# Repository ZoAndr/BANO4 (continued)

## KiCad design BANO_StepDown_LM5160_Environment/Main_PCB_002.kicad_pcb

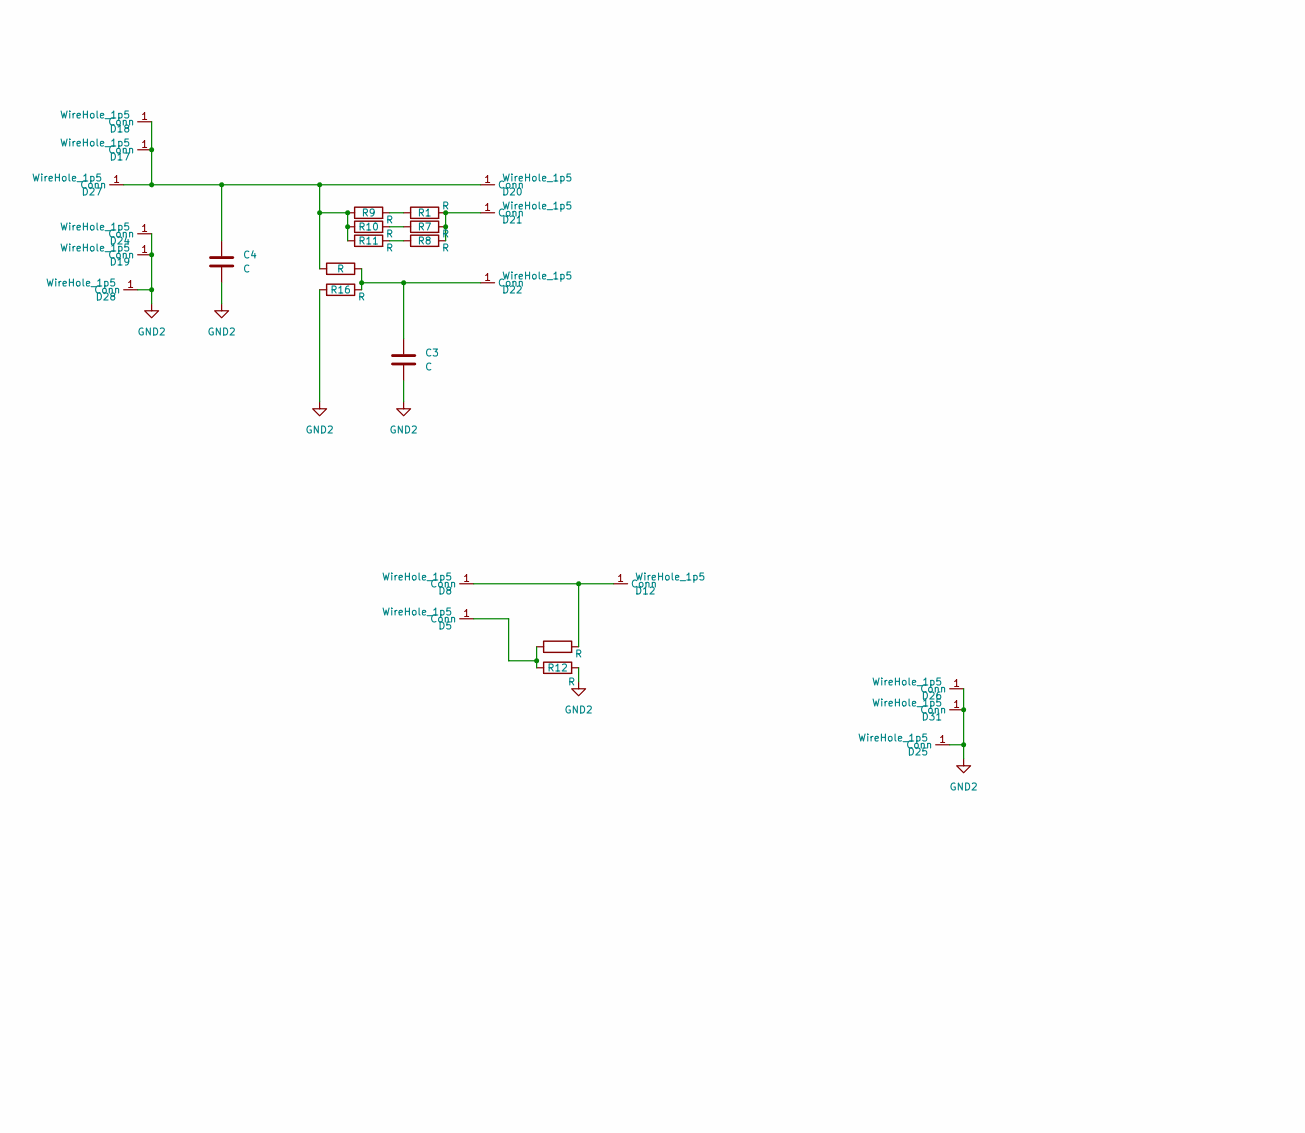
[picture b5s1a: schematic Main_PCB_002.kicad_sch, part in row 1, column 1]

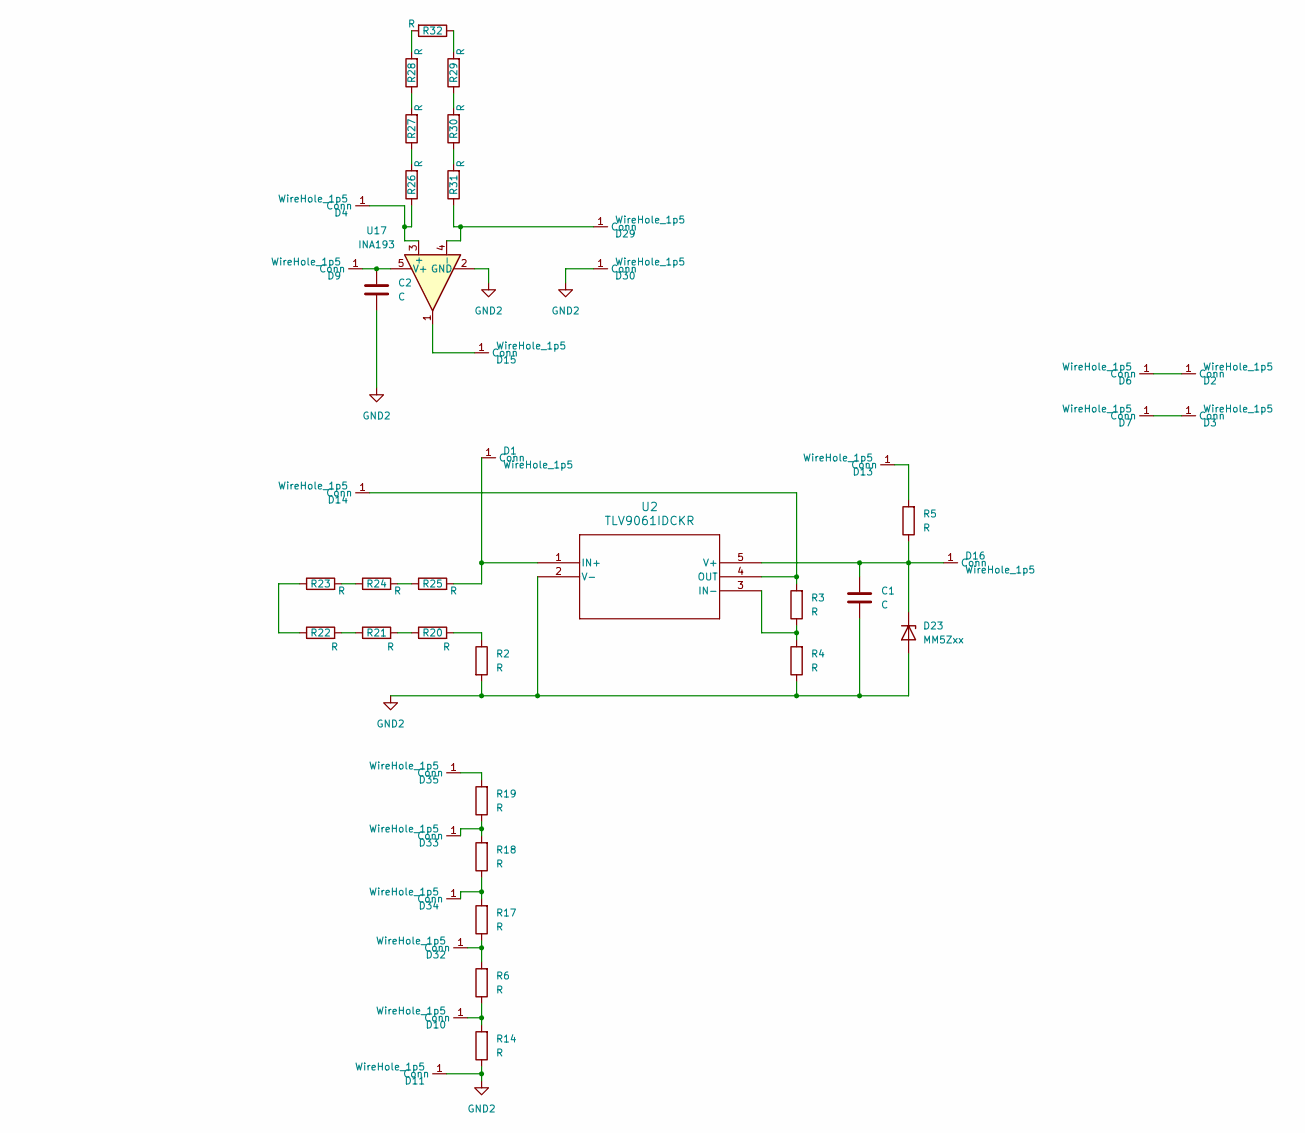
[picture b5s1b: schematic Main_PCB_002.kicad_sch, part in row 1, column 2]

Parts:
C1, C2, C3, C4: C; C_0603_1608Metric_Pad1.08x0.95mm_HandSolder
D1, D2, D3, D4, D5, D6, D7, D8, D9, D10, D11, D12, D13, D14, D15, D16, D17, D18, D19, D20, D21, D22, D24, D25, D26, D27, D28, D29, D30, D31, D32, D33, D34, D35: WireHole_1p5; WireHole_1p2
D23: MM5Zxx; D_SOD-523
R1, R2, R3, R4, R5, R7, R8, R9, R10, R11, R12, R13, R15, R16, R20, R21, R22, R23, R24, R25, R26, R27, R28, R29, R30, R31, R32: R; R_0603_1608Metric_Pad0.98x0.95mm_HandSolder
R6, R14, R17, R18, R19: R; R_2512_6332Metric_Pad1.40x3.35mm_HandSolder
U2: TLV9061IDCKR; DCK5_TEX
U17: INA193; SOT-23-5

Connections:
GND2: C1.2, C2.2, C3.2, C4.2, D11.1 (Conn), D19.1 (Conn), D23.2 (A), D24.1 (Conn), D25.1 (Conn), D26.1 (Conn), D28.1 (Conn), D30.1 (Conn), D31.1 (Conn), R2.2, R4.1, R12.2, R14.1, R16.2, U2.2 (V-), U17.2 (GND)
unnamed: D1.1 (Conn), R25.2, U2.1 (IN+)
unnamed: D2.1 (Conn), D6.1 (Conn)
unnamed: D3.1 (Conn), D7.1 (Conn)
unnamed: D4.1 (Conn), R26.1, U17.3 (+)
unnamed: D5.1 (Conn), R12.1, R13.1
unnamed: C2.1, D9.1 (Conn), U17.5 (V+)
unnamed: D10.1 (Conn), R6.1, R14.2
unnamed: D8.1 (Conn), D12.1 (Conn), R13.2
unnamed: D13.1 (Conn), R5.2
unnamed: D14.1 (Conn), R3.2, U2.4 (OUT)
unnamed: D15.1 (Conn), U17.1
unnamed: C1.1, D16.1 (Conn), D23.1 (K), R5.1, U2.5 (V+)
unnamed: C4.1, D17.1 (Conn), D18.1 (Conn), D20.1 (Conn), D27.1 (Conn), R9.1, R10.1, R11.1, R15.2
unnamed: D21.1 (Conn), R1.2, R7.2, R8.2
unnamed: C3.1, D22.1 (Conn), R15.1, R16.1
unnamed: D29.1 (Conn), R31.1, U17.4 (-)
unnamed: D32.1 (Conn), R6.2, R17.1
unnamed: D33.1 (Conn), R18.2, R19.1
unnamed: D34.1 (Conn), R17.2, R18.1
unnamed: D35.1 (Conn), R19.2
unnamed: R1.1, R9.2
unnamed: R2.1, R20.2
unnamed: R7.1, R10.2
unnamed: R8.1, R11.2
unnamed: R20.1, R21.2
unnamed: R21.1, R22.2
unnamed: R22.1, R23.1
unnamed: R23.2, R24.1
unnamed: R24.2, R25.1
unnamed: R26.2, R27.1
unnamed: R27.2, R28.1
unnamed: R28.2, R32.2
unnamed: R29.1, R30.2
unnamed: R29.2, R32.1
unnamed: R30.1, R31.2
unnamed: R3.1, R4.2, U2.3 (IN-)

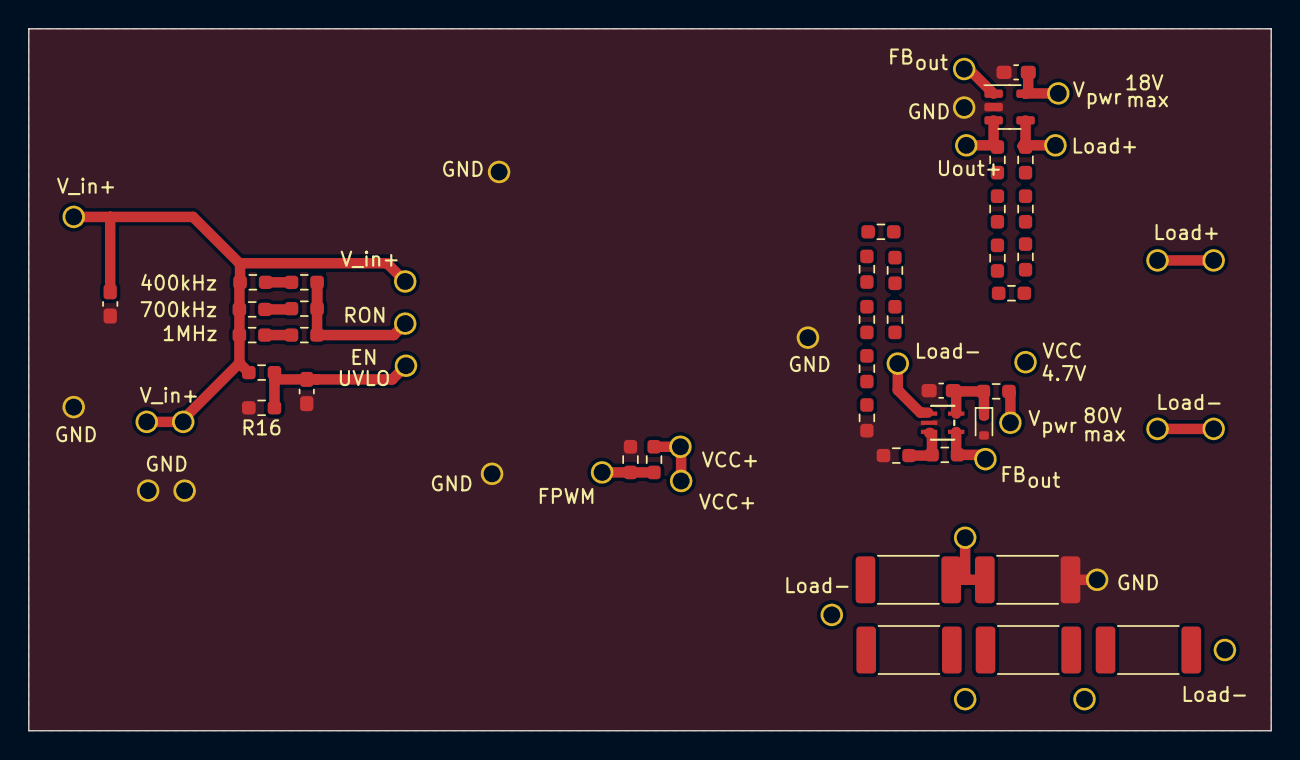
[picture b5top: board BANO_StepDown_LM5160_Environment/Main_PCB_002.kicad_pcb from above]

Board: 2 copper layers, 88.5 x 50.0 mm, 73 parts (0 on the bottom side), 37 nets.

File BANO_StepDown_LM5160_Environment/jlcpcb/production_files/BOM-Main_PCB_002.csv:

Comment,Designator,Footprint,LCSC
R,R3,R_0603_1608Metric_Pad0.98x0.95mm_HandSolder,C103607
R,"R14,R17,R18,R19,R6",R_2512_6332Metric_Pad1.40x3.35mm_HandSolder,C105100
INA193,U17,SOT-23-5,C19548
R,R10,R_0603_1608Metric_Pad0.98x0.95mm_HandSolder,C22795
R,R5,R_0603_1608Metric_Pad0.98x0.95mm_HandSolder,C25586
R,"R15,R9",R_0603_1608Metric_Pad0.98x0.95mm_HandSolder,C25803
R,R4,R_0603_1608Metric_Pad0.98x0.95mm_HandSolder,C25804
MM5Zxx,D23,D_SOD-523,C2832571
C,"C1,C2,C3,C4",C_0603_1608Metric_Pad1.08x0.95mm_HandSolder,C3011705
TLV9061IDCKR,U2,DCK5_TEX,C398357
R,R16,R_0603_1608Metric_Pad0.98x0.95mm_HandSolder,C4184
R,R11,R_0603_1608Metric_Pad0.98x0.95mm_HandSolder,C4197
R,"R2,R20,R21,R22,R23,R24,R25,R26,R27,R28,R29,R30,R31,R32",R_0603_1608Metric_Pad0.98x0.95mm_HandSolder,C705059
WireHole_1p5,D27,WireHole_1p2,
WireHole_1p5,D30,WireHole_1p2,
WireHole_1p5,D29,WireHole_1p2,
WireHole_1p5,D28,WireHole_1p2,
WireHole_1p5,D31,WireHole_1p2,
WireHole_1p5,D26,WireHole_1p2,
WireHole_1p5,D25,WireHole_1p2,
R,R12,R_0603_1608Metric_Pad0.98x0.95mm_HandSolder,
WireHole_1p5,D5,WireHole_1p2,
WireHole_1p5,D9,WireHole_1p2,
WireHole_1p5,D19,WireHole_1p2,
R,R8,R_0603_1608Metric_Pad0.98x0.95mm_HandSolder,
WireHole_1p5,D20,WireHole_1p2,
WireHole_1p5,D2,WireHole_1p2,
WireHole_1p5,D11,WireHole_1p2,
WireHole_1p5,D1,WireHole_1p2,
WireHole_1p5,D17,WireHole_1p2,
WireHole_1p5,D3,WireHole_1p2,
WireHole_1p5,D14,WireHole_1p2,
R,R1,R_0603_1608Metric_Pad0.98x0.95mm_HandSolder,
WireHole_1p5,D22,WireHole_1p2,
R,R13,R_0603_1608Metric_Pad0.98x0.95mm_HandSolder,
WireHole_1p5,D15,WireHole_1p2,
WireHole_1p5,D8,WireHole_1p2,
WireHole_1p5,D13,WireHole_1p2,
R,R7,R_0603_1608Metric_Pad0.98x0.95mm_HandSolder,
WireHole_1p5,D7,WireHole_1p2,
WireHole_1p5,D24,WireHole_1p2,
WireHole_1p5,D6,WireHole_1p2,
WireHole_1p5,D16,WireHole_1p2,
WireHole_1p5,D12,WireHole_1p2,
WireHole_1p5,D21,WireHole_1p2,
WireHole_1p5,D4,WireHole_1p2,
WireHole_1p5,D10,WireHole_1p2,
WireHole_1p5,D18,WireHole_1p2,
WireHole_1p5,D35,WireHole_1p2,
WireHole_1p5,D34,WireHole_1p2,
WireHole_1p5,D33,WireHole_1p2,
WireHole_1p5,D32,WireHole_1p2,

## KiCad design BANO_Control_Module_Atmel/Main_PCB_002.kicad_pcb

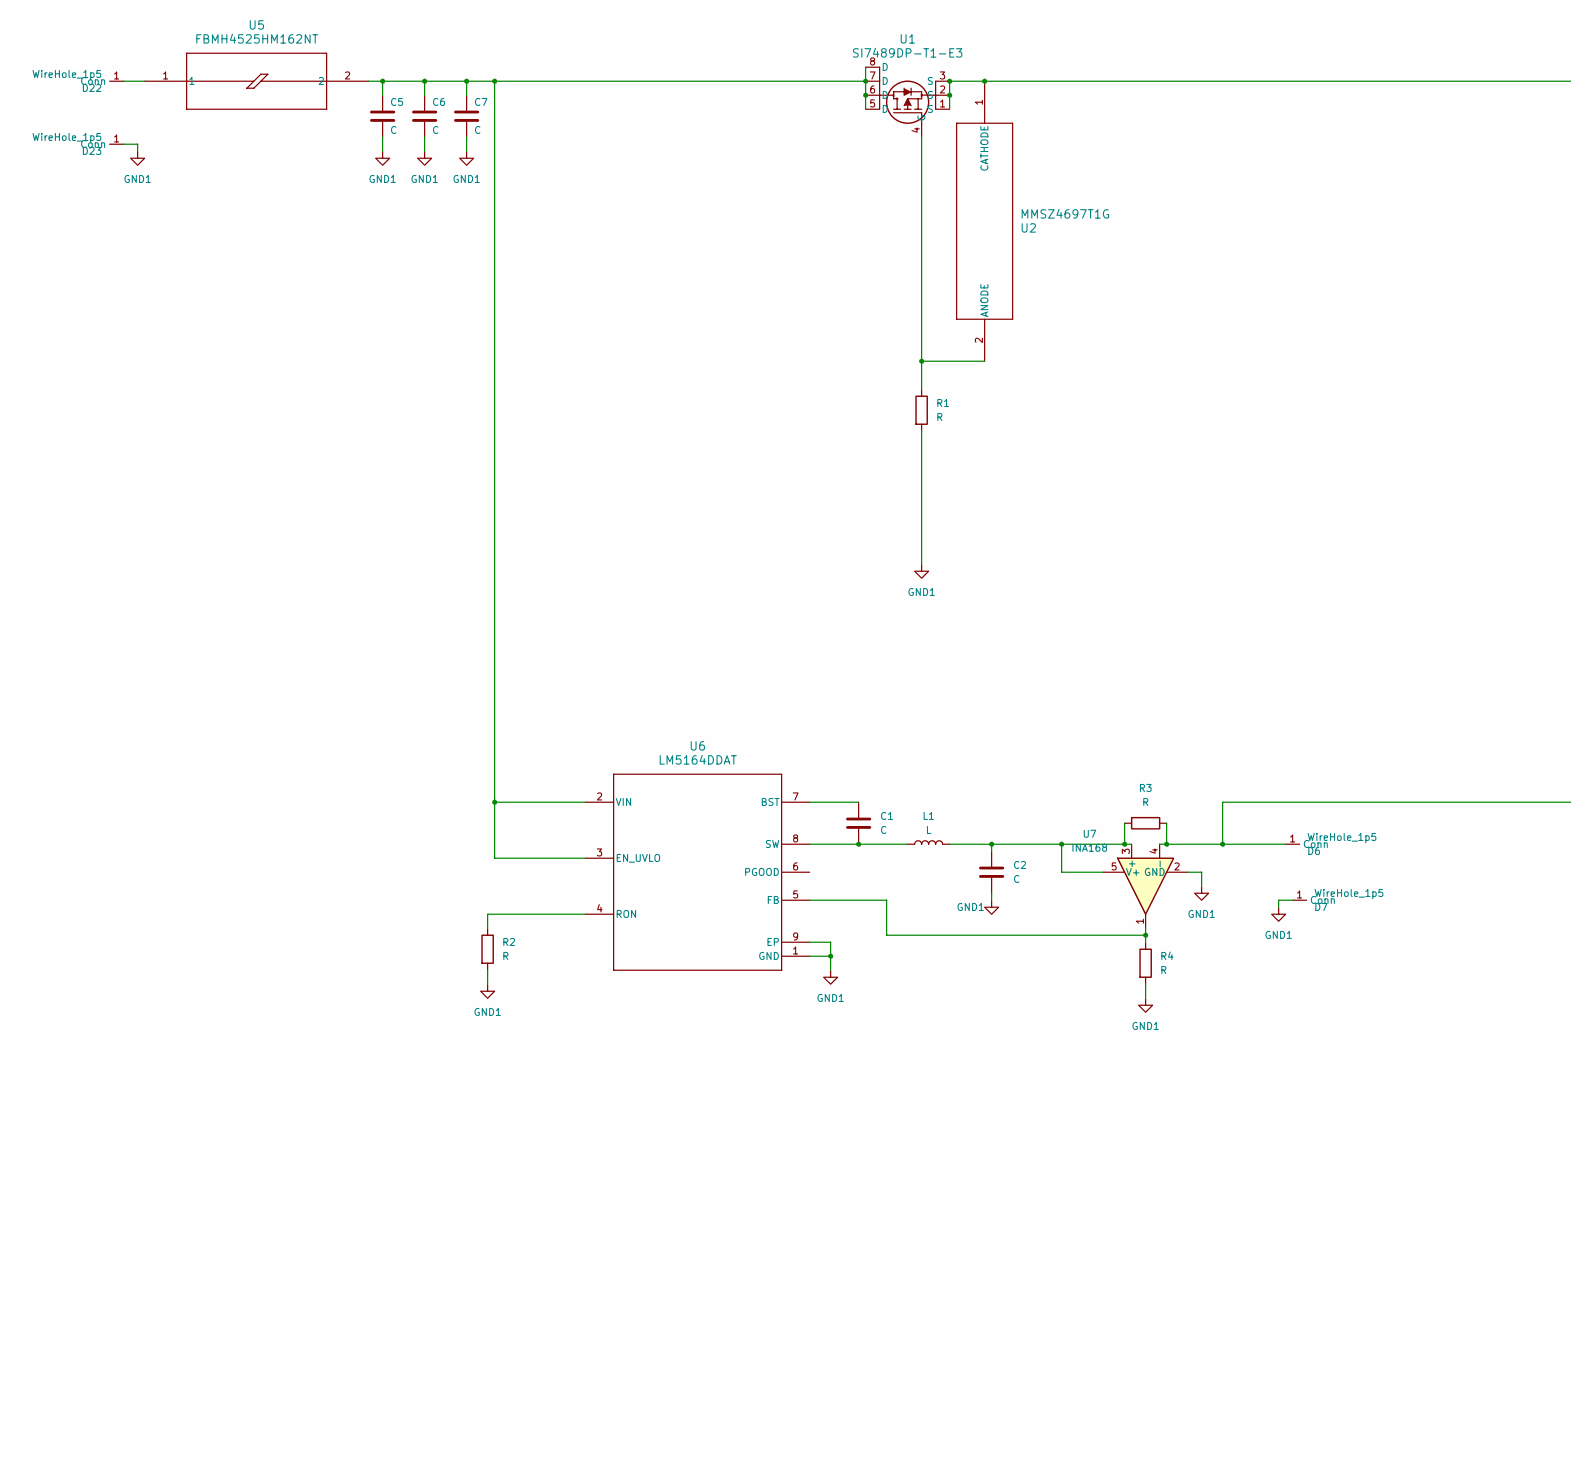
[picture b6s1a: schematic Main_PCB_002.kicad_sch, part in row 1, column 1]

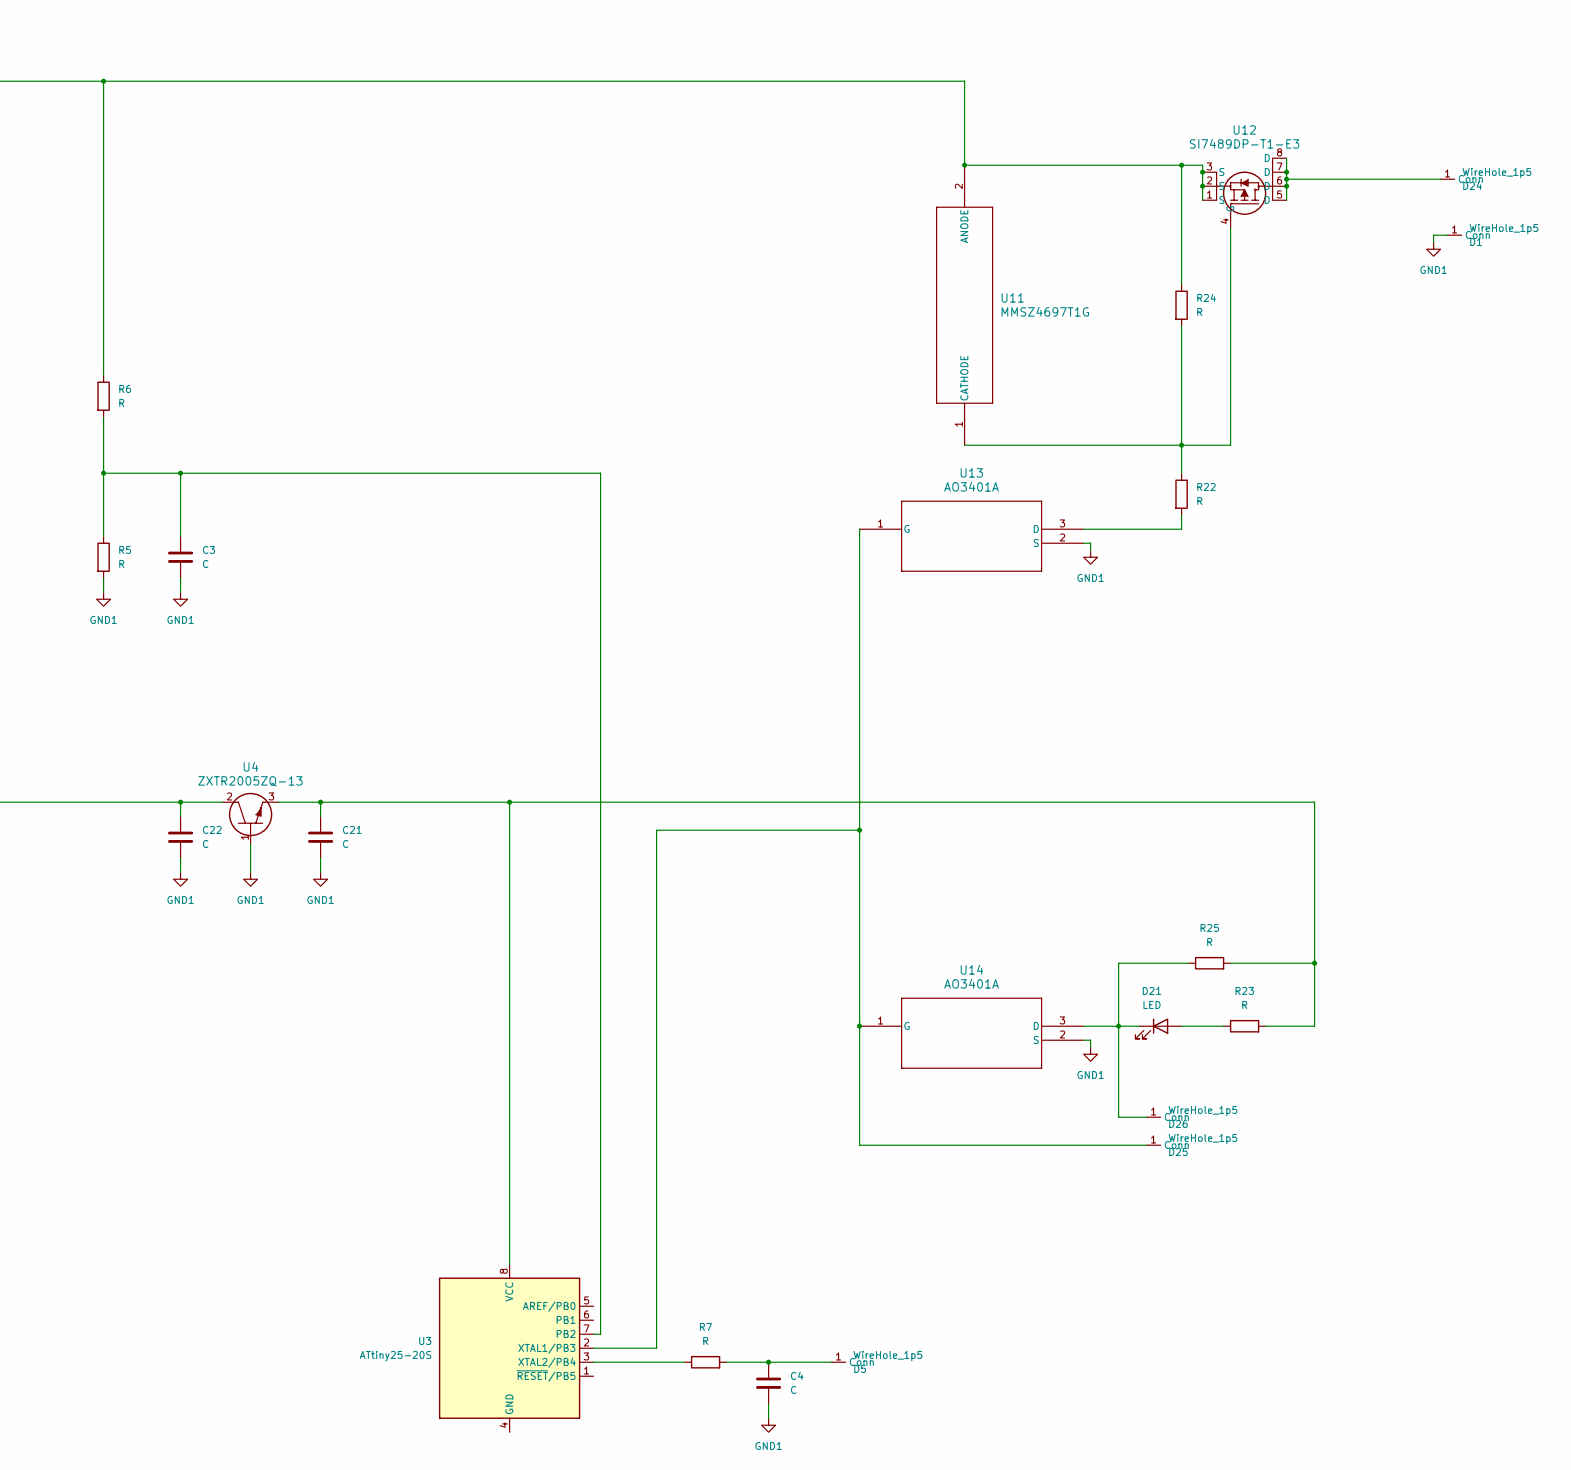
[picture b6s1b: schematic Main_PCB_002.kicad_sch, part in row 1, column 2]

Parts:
C1, C2, C3, C4, C5, C6, C7, C21, C22: C; C_0805_2012Metric_Pad1.18x1.45mm_HandSolder
D1, D5, D6, D7, D22, D23, D24, D25, D26: WireHole_1p5; WireHole_1p2
D21: LED; LED_0603_1608Metric_Pad1.05x0.95mm_HandSolder
L1: L; IND_VLS3012HBX-3R3M_TDK-L
R1, R2, R3, R4, R5, R6, R7, R22, R23, R24, R25: R; R_0603_1608Metric_Pad0.98x0.95mm_HandSolder
U1, U12: SI7489DP-T1-E3; MOSFET_65DP-T1-E3_VIS
U2, U11: MMSZ4697T1G; SOD-123_ONS
U3: ATtiny25-20S; SOIC-8W_5.3x5.3mm_P1.27mm
U4: ZXTR2005ZQ-13; SOT-89_4P5X2P45_DIO
U5: FBMH4525HM162NT; FBMH4525HM162NT_TAY
U6: LM5164DDAT; DDA0008E-IPC_A
U7: INA168; SOT-23-5
U13, U14: AO3401A; SOT-23-3L_AOS

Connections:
GND1: C2.2, C3.2, C4.2, C5.2, C6.2, C7.2, C21.2, C22.2, D1.1 (Conn), D7.1 (Conn), D23.1 (Conn), R1.2, R2.2, R4.2, R5.2, U4.1, U6.1 (GND), U6.9 (EP), U7.2 (GND), U13.2 (S), U14.2 (S)
unnamed: C4.1, D5.1 (Conn), R7.2
unnamed: C22.1, D6.1 (Conn), R3.1, U4.2, U7.4 (-)
unnamed: D21.2 (A), R23.1
unnamed: D21.1 (K), D26.1 (Conn), R25.1, U14.3 (D)
unnamed: D22.1 (Conn), U5.1
unnamed: D24.1 (Conn), U12.5 (D), U12.6 (D), U12.7 (D), U12.8 (D)
unnamed: D25.1 (Conn), U3.2 (XTAL1/PB3), U13.1 (G), U14.1 (G)
unnamed: R1.1, U1.4 (G), U2.2 (ANODE)
unnamed: C3.1, R5.1, R6.2, U3.7 (PB2)
unnamed: C21.1, R23.2, R25.2, U3.8 (VCC), U4.3
unnamed: R7.1, U3.3 (XTAL2/PB4)
unnamed: C1.1, U6.7 (BST)
unnamed: C5.1, C6.1, C7.1, U1.5 (D), U1.6 (D), U1.7 (D), U1.8 (D), U5.2, U6.2 (VIN), U6.3 (EN_UVLO)
unnamed: R4.1, U6.5 (FB), U7.1
unnamed: R2.1, U6.4 (RON)
unnamed: C1.2, L1.1, U6.8 (SW)
unnamed: C2.1, L1.2, R3.2, U7.3 (+), U7.5 (V+)
unnamed: R6.1, R24.1, U1.1 (S), U1.2 (S), U1.3 (S), U2.1 (CATHODE), U11.2 (ANODE), U12.1 (S), U12.2 (S), U12.3 (S)
unnamed: R22.1, R24.2, U11.1 (CATHODE), U12.4 (G)
unnamed: R22.2, U13.3 (D)

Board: 2 copper layers, 42 parts (0 on the bottom side), 21 nets, no tracks yet.

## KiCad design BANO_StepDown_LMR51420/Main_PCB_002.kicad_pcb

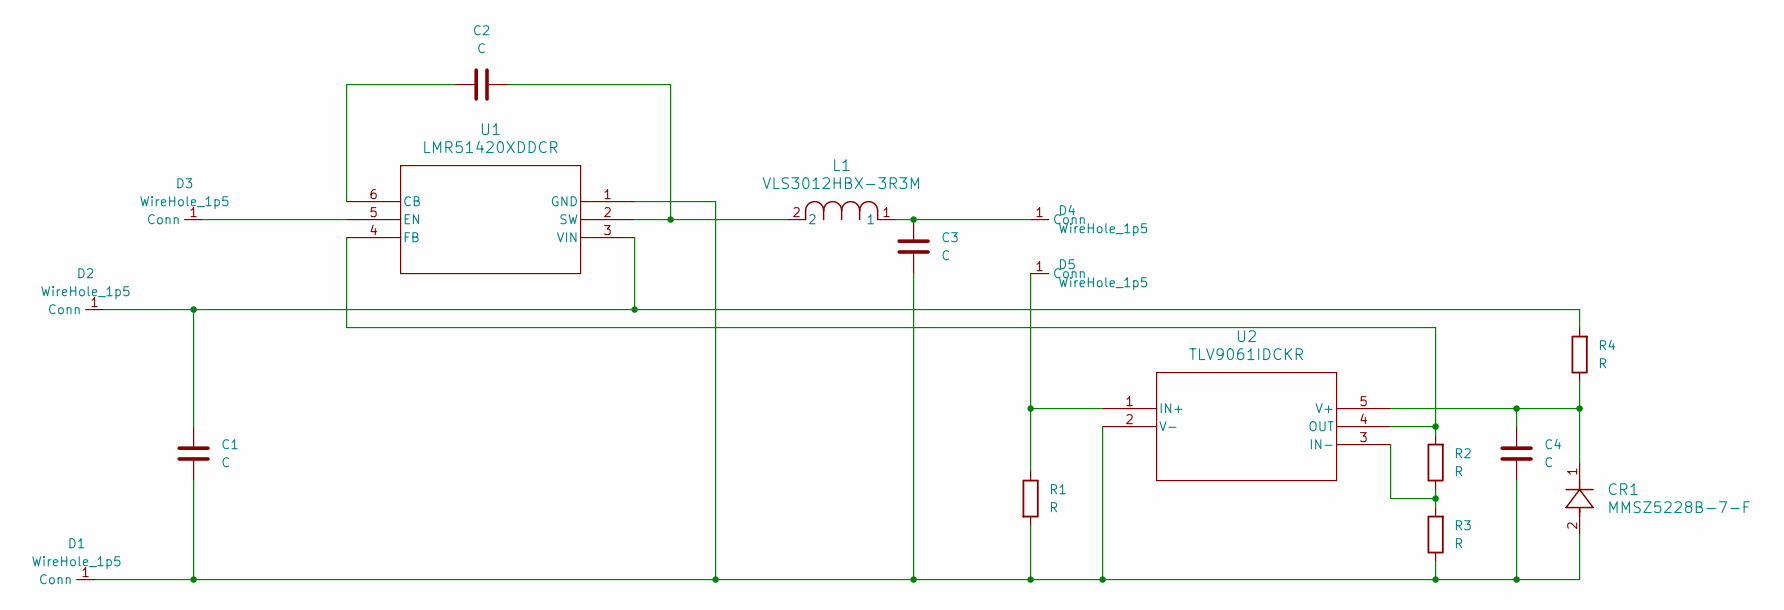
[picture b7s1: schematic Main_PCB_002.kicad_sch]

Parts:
C1, C3: C; C_0805_2012Metric_Pad1.18x1.45mm_HandSolder
C2, C4: C; C_0603_1608Metric_Pad1.08x0.95mm_HandSolder
CR1: MMSZ5228B-7-F; SOD123_DIO
D1, D2, D3, D4, D5: WireHole_1p5; WireHole_1p2
L1: VLS3012HBX-3R3M; IND_VLS3012HBX-3R3M_TDK
R1, R2, R3, R4: R; R_0603_1608Metric_Pad0.98x0.95mm_HandSolder
U1: LMR51420XDDCR; SOT23_DDC_TEX
U2: TLV9061IDCKR; DCK5_TEX

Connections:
unnamed: C1.2, C3.2, C4.2, CR1.2, D1.1 (Conn), R1.2, R3.1, U1.1 (GND), U2.2 (V-)
unnamed: C1.1, D2.1 (Conn), R4.2, U1.3 (VIN)
unnamed: D3.1 (Conn), U1.5 (EN)
unnamed: C3.1, D4.1 (Conn), L1.1
unnamed: D5.1 (Conn), R1.1, U2.1 (IN+)
unnamed: C2.1, U1.6 (CB)
unnamed: R2.2, U1.4 (FB), U2.4 (OUT)
unnamed: C2.2, L1.2, U1.2 (SW)
unnamed: R2.1, R3.2, U2.3 (IN-)
unnamed: C4.1, CR1.1, R4.1, U2.5 (V+)

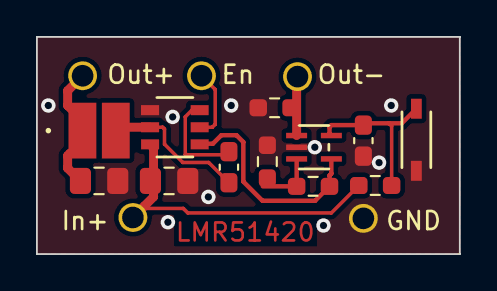
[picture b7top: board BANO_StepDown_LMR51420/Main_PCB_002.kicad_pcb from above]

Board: 2 copper layers, 23.5 x 12.1 mm, 17 parts (0 on the bottom side), 10 nets.

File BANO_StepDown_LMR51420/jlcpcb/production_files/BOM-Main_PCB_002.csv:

Comment,Designator,Footprint,LCSC
R,R1,R_0603_1608Metric_Pad0.98x0.95mm_HandSolder,C126169
C,"C2,C4",C_0603_1608Metric_Pad1.08x0.95mm_HandSolder,C15849
R,R4,R_0603_1608Metric_Pad0.98x0.95mm_HandSolder,C21190
R,R3,R_0603_1608Metric_Pad0.98x0.95mm_HandSolder,C25804
R,R2,R_0603_1608Metric_Pad0.98x0.95mm_HandSolder,C25811
TLV9061IDCKR,U2,DCK5_TEX,C398357
VLS3012HBX-3R3M,L1,IND_VLS3012HBX-3R3M_TDK,C404495
C,"C1,C3",C_0805_2012Metric_Pad1.18x1.45mm_HandSolder,C440198
MMSZ5228B-7-F,CR1,SOD123_DIO,C513125
LMR51420XDDCR,U1,SOT23_DDC_TEX,C5383002
WireHole_1p5,D4,WireHole_1p2,
WireHole_1p5,D1,WireHole_1p2,
WireHole_1p5,D5,WireHole_1p2,
WireHole_1p5,D2,WireHole_1p2,
WireHole_1p5,D3,WireHole_1p2,
